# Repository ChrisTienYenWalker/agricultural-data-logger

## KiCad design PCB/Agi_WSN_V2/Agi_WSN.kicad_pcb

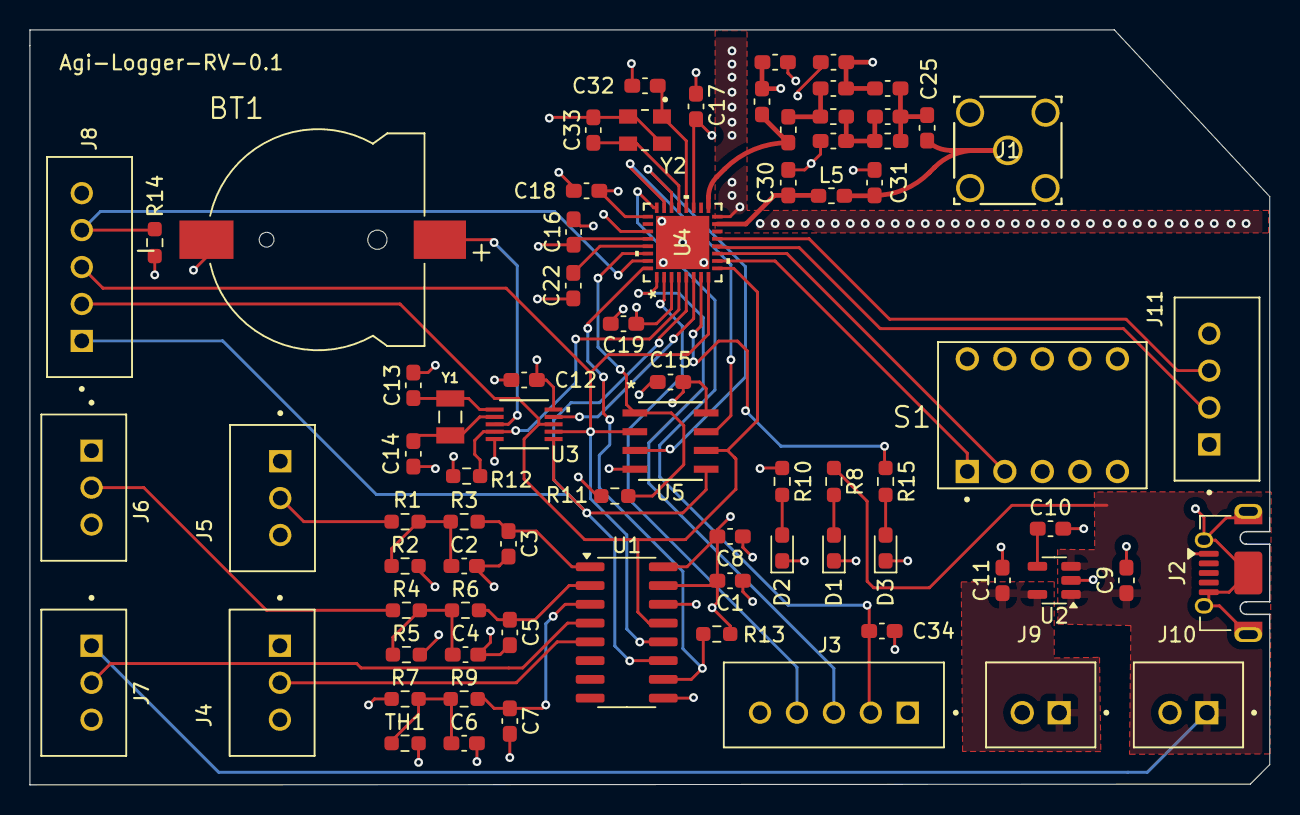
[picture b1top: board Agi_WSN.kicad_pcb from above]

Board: 4 copper layers, 83.9 x 51.1 mm, 76 parts (0 on the bottom side), 47 nets.

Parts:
BT1: BC501SM; BAT_BC501SM
C1, C8, C12, C15, C16, C17, C18, C19, C22, C34: 100nF; C_0603_1608Metric_Pad1.08x0.95mm_HandSolder
C2, C3, C4, C5, C10, C23, C24, C25, C26, C27, C28, C29, C30, C31: C; C_0603_1608Metric_Pad1.08x0.95mm_HandSolder
C6, C7: 330nF; C_0603_1608Metric_Pad1.08x0.95mm_HandSolder
C9: 1uF; C_0603_1608Metric_Pad1.08x0.95mm_HandSolder
C11: 2.2uF; C_0603_1608Metric_Pad1.08x0.95mm_HandSolder
C13, C14: 12.5pF; C_0603_1608Metric_Pad1.08x0.95mm_HandSolder
C32, C33: 8pF; C_0603_1608Metric_Pad1.08x0.95mm_HandSolder
D1, D2, D3: LED; LED_0603_1608Metric_Pad1.05x0.95mm_HandSolder
J1: RF2-04A-T-00-50-G; CONN_RF2-04A-T-00-50-G_ADM
J2: USB_B_Micro; USB_Micro-AB_Molex_47590-0001
J3, J8: B5B-XH-A; JST_B5B-XH-A
J4, J5, J6, J7: B3B-XH-A; JST_B3B-XH-A
J9, J10: B2B-XH-A; JST_B2B-XH-A
J11: B4B-XH-A; JST_B4B-XH-A
L1, L2, L3, L4, L5: L; L_0603_1608Metric_Pad1.05x0.95mm_HandSolder
R1, R2, R3, R4, R5, R6: R; R_0603_1608Metric_Pad0.98x0.95mm_HandSolder
R7, R9, R11, R12, R13, R14: 10k; R_0603_1608Metric_Pad0.98x0.95mm_HandSolder
R8, R10, R15: 1k; R_0603_1608Metric_Pad0.98x0.95mm_HandSolder
S1: DS01C-254-S-05BE; SW_DS01C-254-S-05BE
TH1: Thermistor; R_0603_1608Metric_Pad0.98x0.95mm_HandSolder
U1: MCP3208; SOIC-16_3.9x9.9mm_P1.27mm
U2: SPX3819M5-L-3-3; SOT-23-5
U3: MCP79510T-I/MS; MCP79510T_I_MS-L
U4: STM32WL30KBV6; STM32WL30KBV6-L
U5: M95320-WMN6TP; M95320_WMN6TP-L
Y1: ABS07-32.768KHZ-T; XTAL_ABS07-32.768KHZ-T
Y2: CX3225SB48000D0FPJC1; OSCCC320X250X60N

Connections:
!W: U4.22 (PA1), U5.3 (*W)
+3.3V: C1.1, C8.1, C11.1, C12.1, C15.1, C16.1, C17.1, C18.1, C19.1, C28.1, C29.1, J3.1, J4.1, J5.1, J6.1, J9.1, J11.1, L4.2, R7.1, R10.1, R11.1, R12.1, R13.1, R14.1, U1.15 (Vref), U1.16 (Vdd), U2.5 (OUT), U3.10 (VCC), U4.3 (VDD_1), U4.19 (VDDRF), U4.25 (VDDSD), U4.28 (VFBSD), U5.8 (VCC)
+5V: C9.1, J2.1 (VBUS), J7.1, J10.1, R8.1, U2.1 (IN), U2.3 (EN)
/MCU/DIP0: S1.1A, U4.10 (PB12)
/MCU/DIP1: S1.2A, U4.11 (PB13)
/MCU/LED: R15.1, U4.7 (PA9)
/Sensors/A: C3.1, R3.2, U1.1 (CH0)
/Sensors/B: C5.1, R6.2, U1.2 (CH1)
/Sensors/Therm: C7.1, R9.2, U1.3 (CH2)
ADC_CS: R13.2, U1.10 (~CS/SHDN), U4.32 (PB2)
EEPROM_CS: R11.2, U4.30 (PB0), U5.1 (*S)
EXT_CS: J8.4, R14.2, U4.31 (PB1)
GND: BT1.N, C1.2, C2.2, C3.2, C4.2, C5.2, C6.2, C7.2, C8.2, C9.2, C10.2, C11.2, C12.2, C13.2, C14.2, C15.2, C16.2, C17.2, C18.2, C19.2, C22.2, C23.2, C24.2, C27.2, C28.2, C29.2, C30.2, C31.2, C32.2, C33.2, C34.2, D1.1 (K), D2.1 (K), D3.1 (K), J1.2, J1.3, J1.4, J1.5, J2.5 (GND), J2.6 (Shield), J3.5, J4.3, J5.3, J6.3, J7.3, J8.5, J9.2, J10.2, J11.4, R2.2, R5.2, S1.1B, S1.2B, S1.3B, S1.4B, S1.5B, TH1.2, U1.9 (DGND), U1.14 (AGND), U2.2 (GND), U3.5 (VSS), U4.16 (EXTGND), U4.27 (VSSSD), U4.33 (EPAD), U5.4 (VSS), Y2.2 (GND), Y2.4 (GND__1)
HOLD: U4.23 (PB7), U5.7 (*HOLD)
Input A: J6.2, R4.1
Input B: J5.2, R1.1
MFP: U3.9 (MFP), U4.6 (PA10)
NRST: C34.1, J3.2, U4.24 (NRST)
unnamed: C2.1, R1.2, R2.1, R3.1
unnamed: C4.1, R4.2, R5.1, R6.1
unnamed: C6.1, R7.2, R9.1, TH1.1
unnamed: C23.1, C25.1, C26.2, L1.2
unnamed: C24.1, C26.1, L1.1, L2.2
unnamed: C25.2, C31.1, J1.1, L5.2
unnamed: C27.1, L2.1, L3.2
unnamed: D1.2 (A), R8.2
unnamed: D2.2 (A), R10.2
unnamed: D3.2 (A), R15.2
unnamed: C10.1, U2.4 (BP)
unnamed: BT1.P, U3.3 (VBAT)
unnamed: C13.1, U3.1 (X1), Y1.1
unnamed: C14.1, U3.2 (X2), Y1.2
unnamed: C33.1, U4.21 (OSCIN), Y2.3
unnamed: C32.1, U4.20 (OSCOUT), Y2.1
unnamed: C30.1, L5.1, U4.15 (RX)
unnamed: L3.1, L4.1, U4.17 (TX_HP)
unnamed: C22.1, U4.29 (VCAP)
RTC_CS: R12.2, U3.4 (*CS), U4.4 (PA0)
SCK: J8.2, U1.13 (CLK), U3.8 (SCK), U4.9 (PB6), U5.6 (C)
SI: J8.1, U1.11 (Din), U3.6 (SI), U4.5 (PA11), U5.5 (D)
SO: J8.3, U1.12 (Dout), U3.7 (SO), U4.8 (PA8), U5.2 (Q)
SWCLK: J3.4, U4.2 (PA3)
SWDIO: J3.3, U4.1 (PA2)
Sensor C(3.3V): J4.2, U1.5 (CH4)
Sensor C(5V): J7.2, U1.4 (CH3)
UART_RX: J11.2, U4.12 (PB14)
UART_TX: J11.3, U4.13 (PB15)

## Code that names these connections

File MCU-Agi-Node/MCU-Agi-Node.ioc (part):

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Mcu.Name=STM32WL30KBVx
Mcu.Package=VFQFPN32
Mcu.UserName=STM32WL30KBVx
PA10.GPIOParameters=GPIO_Label
PA10.GPIO_Label=CS1
PA10.Signal=GPIO_Output
PA11.Mode=Full_Duplex_Master
PA11.Signal=SPI3_MOSI
PA2.Mode=Serial_Wire
PA2.Signal=DEBUG_SWDIO
PA3.Mode=Serial_Wire
PA3.Signal=DEBUG_SWCLK
PA8.Mode=Full_Duplex_Master
PA8.Signal=SPI3_MISO
PA9.GPIOParameters=GPIO_Label
PA9.GPIO_Label=CS2
PA9.Signal=GPIO_Output
PB0.GPIOParameters=GPIO_Label
PB0.GPIO_Label=DIP2
PB0.Signal=GPIO_Input
PB1.GPIOParameters=GPIO_Label
PB1.GPIO_Label=DIP1
PB1.Signal=GPIO_Input
PB14.Mode=Asynchronous
PB14.Signal=USART1_RX
PB15.Mode=Asynchronous
PB15.Signal=USART1_TX
PB2.GPIOParameters=GPIO_Label
PB2.GPIO_Label=DIP0
PB2.Signal=GPIO_Input
PB6.Mode=Full_Duplex_Master
PB6.Signal=SPI3_SCK
RCC.HSE_VALUE=48000000
board=custom

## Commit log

2025-10-14 added base files for project
2025-10-15 made base GUI
2025-12-06 PCB Files
2025-12-09 Base setup for the GUI and removal of old MCU Node
2025-12-09 base for debug gui
2025-12-11 added lora drivers and uart transmission
2025-12-11 new debug page
2026-01-02 PCB V2
2026-01-02 wrote base code for ADC and RTC
